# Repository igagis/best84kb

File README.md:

# best84kb
custom 84 keys keyboard project

# Ubuntu

install `gcc-avr`, `avr-libc`, `dfu-programmer`, `avrdude` packages via apt

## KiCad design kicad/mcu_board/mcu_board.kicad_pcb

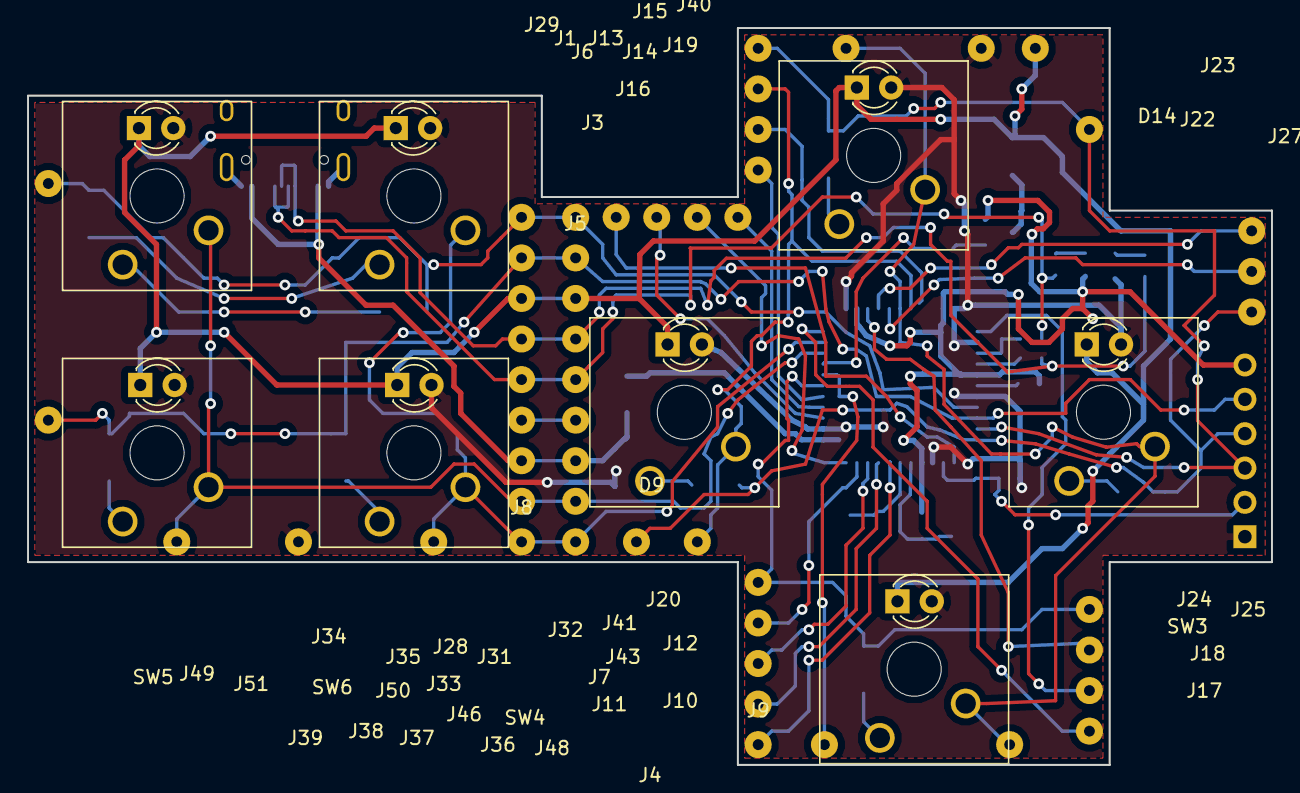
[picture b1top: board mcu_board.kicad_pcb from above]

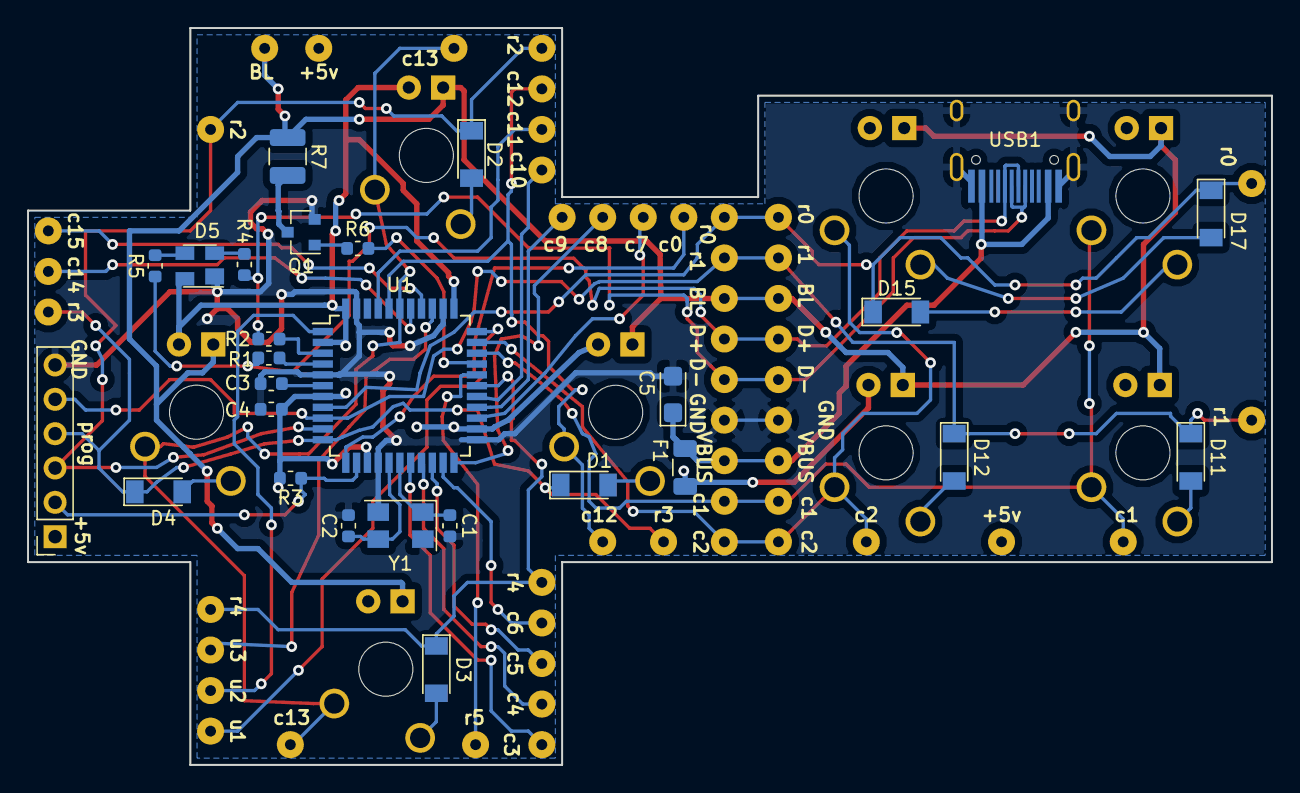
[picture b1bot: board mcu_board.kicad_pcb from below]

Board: 2 copper layers, 92.0 x 54.5 mm, 94 parts (27 on the bottom side), 50 nets.

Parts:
C1, C2: 22pF; C_0603_1608Metric
C3: 1uF; C_0603_1608Metric
C4: 100nF; C_0603_1608Metric
C5: 22uF; CP_EIA-3216-18_Kemet-A
D1, D2, D3, D4, D11, D12, D15, D17: LL4148; D_MiniMELF
D5: PRTR5V0U2X; SOT-143
D6, D7, D8, D9, D10, D13, D14, D16: LED; LED_D3.0mm
F1: 500mA; Fuse_1206_3216Metric
J1, J3, J4, J5, J6, J7, J8, J9, J10, J11, J12, J13, J14, J15, J16, J17, J18, J19, J20, J21, J22, J23, J24, J25, J26, J27, J28, J29, J30, J31, J32, J33, J34, J35, J36, J37, J38, J39, J40, J41, J42, J43, J44, J45, J46, J47, J48, J49, J50, J51, J52: Conn_01x01_Female; SolderWirePad_1x01_Drill0.8mm
J2: Conn_01x06_Female; PinSocket_1x06_P2.54mm_Vertical
Q1: BC817, MMBTA42; SOT-23
R1, R2: 22R; R_0603_1608Metric
R3, R6: 10k; R_0603_1608Metric
R4, R5: 5.1k; R_0603_1608Metric
R7: 10R; R_1210_3225Metric
SW1, SW4, SW5, SW6, SW7, SW8: SW_Push; SW_Cherry_MX1A_1.00u_Plate
SW2: SW_Push; SW_Cherry_MX1A_1.75u_Plate
SW3: SW_Push; SW_Cherry_MX1A_2.25u_Plate
U1: ATmega32U4-AU; TQFP-44_10x10mm_P0.8mm
USB1: HRO-TYPE-C-31-M-12; HRO-TYPE-C-31-M-12-HandSoldering
Y1: 8MHz; Crystal_SMD_5032-4Pin_5.0x3.2mm

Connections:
+5V: C4.2, D5.4, D6.2, D7.2, D8.2, D9.2, D10.2, D13.2, D14.2, D16.2, F1.1, J2.1, J51.1, J52.1, R3.2, U1.2, U1.7, U1.14, U1.24, U1.34, U1.44
/BL_cathode: D6.1, D7.1, D8.1, D9.1, D10.1, D13.1, D14.1, D16.1, J3.1, J28.1, J42.1, R7.1
/D+: J33.1, J39.1, R1.2, R5.1, USB1.6, USB1.8
/D-: J34.1, J38.1, R2.2, R4.1, USB1.5, USB1.7
/VBUS: C5.1, F1.2, J35.1, J36.1, USB1.2, USB1.11
/backlight: R6.2, U1.30
/col_0: J6.1, U1.12
/col_1: J7.1, J31.1, J49.1, SW5.2, SW7.2, U1.31
/col_2: J8.1, J32.1, J50.1, SW6.2, SW8.2, U1.32
/col_3: J9.1, U1.18
/col_4: J10.1, U1.19
/col_5: J11.1, U1.20
/col_6: J12.1, U1.21
/col_7: J13.1, U1.25
/col_8: J14.1, U1.22
/col_9: J15.1, U1.26
/col_10: J16.1, U1.27
/col_11: J19.1, U1.41
/col_12: J20.1, J40.1, SW4.2, U1.40
/col_13: J21.1, J44.1, SW1.2, SW2.2, SW3.2, U1.39
/col_14: J22.1, U1.38
/col_15: J23.1, U1.37
/row_0: D15.1, D17.1, J1.1, J29.1, J47.1, U1.8
/row_1: D11.1, D12.1, J2.5, J5.1, J30.1, J46.1, U1.9
/row_2: D2.1, J2.3, J26.1, J45.1, U1.10
/row_3: D1.1, D4.1, J2.4, J27.1, J41.1, U1.11
/row_4: D3.1, J25.1, J43.1, U1.28
/row_5: J4.1, U1.29
/unused_1: J17.1, U1.33
/unused_2: J18.1, U1.1
/unused_3: J24.1, U1.36
GND: C1.2, C2.2, C3.2, C4.1, C5.2, D5.1, J2.6, J37.1, J48.1, Q1.2, U1.5, U1.15, U1.23, U1.35, U1.43, USB1.1, USB1.12, USB1.13, Y1.2, Y1.4
unnamed: C1.1, U1.17, Y1.1
unnamed: C2.1, U1.16, Y1.3
unnamed: C3.1, U1.6
unnamed: D1.2, SW4.1
unnamed: D2.2, SW1.1
unnamed: D3.2, SW2.1
unnamed: D4.2, SW3.1
unnamed: D5.2, R4.2
unnamed: D5.3, R5.2
unnamed: D11.2, SW5.1
unnamed: D12.2, SW6.1
unnamed: D15.2, SW7.1
unnamed: D17.2, SW8.1
unnamed: J2.2, R3.1, U1.13
unnamed: Q1.1, R6.1
unnamed: Q1.3, R7.2
unnamed: R1.1, U1.4
unnamed: R2.1, U1.3

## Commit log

2020-01-12 kicad project added
2020-01-12 added submodules
2020-01-12 submodule corrected
2020-01-12 use custom usb type c lib
2020-01-12 fixed quartz symbol (use 4 pin one)
2020-01-12 added connectors to all gpio's
2020-01-13 kbfirmware.com json
2020-01-13 added connectors to SPI pins
2020-01-13 added 4 keys and diodes
2020-01-15 added USB ESD protection and power fuse
2020-01-15 schematics
2020-01-15 stuff
2020-01-15 added function key
2020-01-15 added 4 keys around USB connector
2020-01-16 some pcb arrangement
2020-01-16 gerber build
2020-02-02 add PAUSE to 2nd layer
2020-02-26 added atmega32u4 bootloaders
2020-02-26 flash fuses script
2020-02-26 read fuses script
2020-02-27 read flash script
2020-02-29 qmk firmware
2020-11-11 remove absolute path
2021-09-13 set brown-out detection fuse to 4.3V to make chip reset on power on
2023-02-25 add instructions about which packages to install in order to build
